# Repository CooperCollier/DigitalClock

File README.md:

# DigitalClock
A 12-hour digital clock made out of logic gates and flip-flops and implemented in Logisim.

This project incorporates the logisim 7-segment-display driver created here: https://github.com/marceloboeira/logisim-7-segment-display-driver.

How to open this project:

1: clone this repository with `git clone https://github.com/CooperCollier/DigitalClock --recursive`. The recursive tag is necessary to include the 7-segment-display driver.

2: Open the file clock.circ in logisim.

3: Under the 'simulate' tab, set 'tick frequency' to 2Hz.

4: Under the 'simulate' tab, set 'ticks enabled' to true.

How to use the clock:

Press the SET TIME button to make the clock enter or exit the SET TIME state. When the clock is in the SET TIME state, the SET TIME LED will be turned on. When the clock enters the SET TIME state, the time is immediately reset to 12:00 AM. 

Press the +MIN and +HOUR buttons to change the displayed time. These buttons are only active when the clock is in the SET TIME state.

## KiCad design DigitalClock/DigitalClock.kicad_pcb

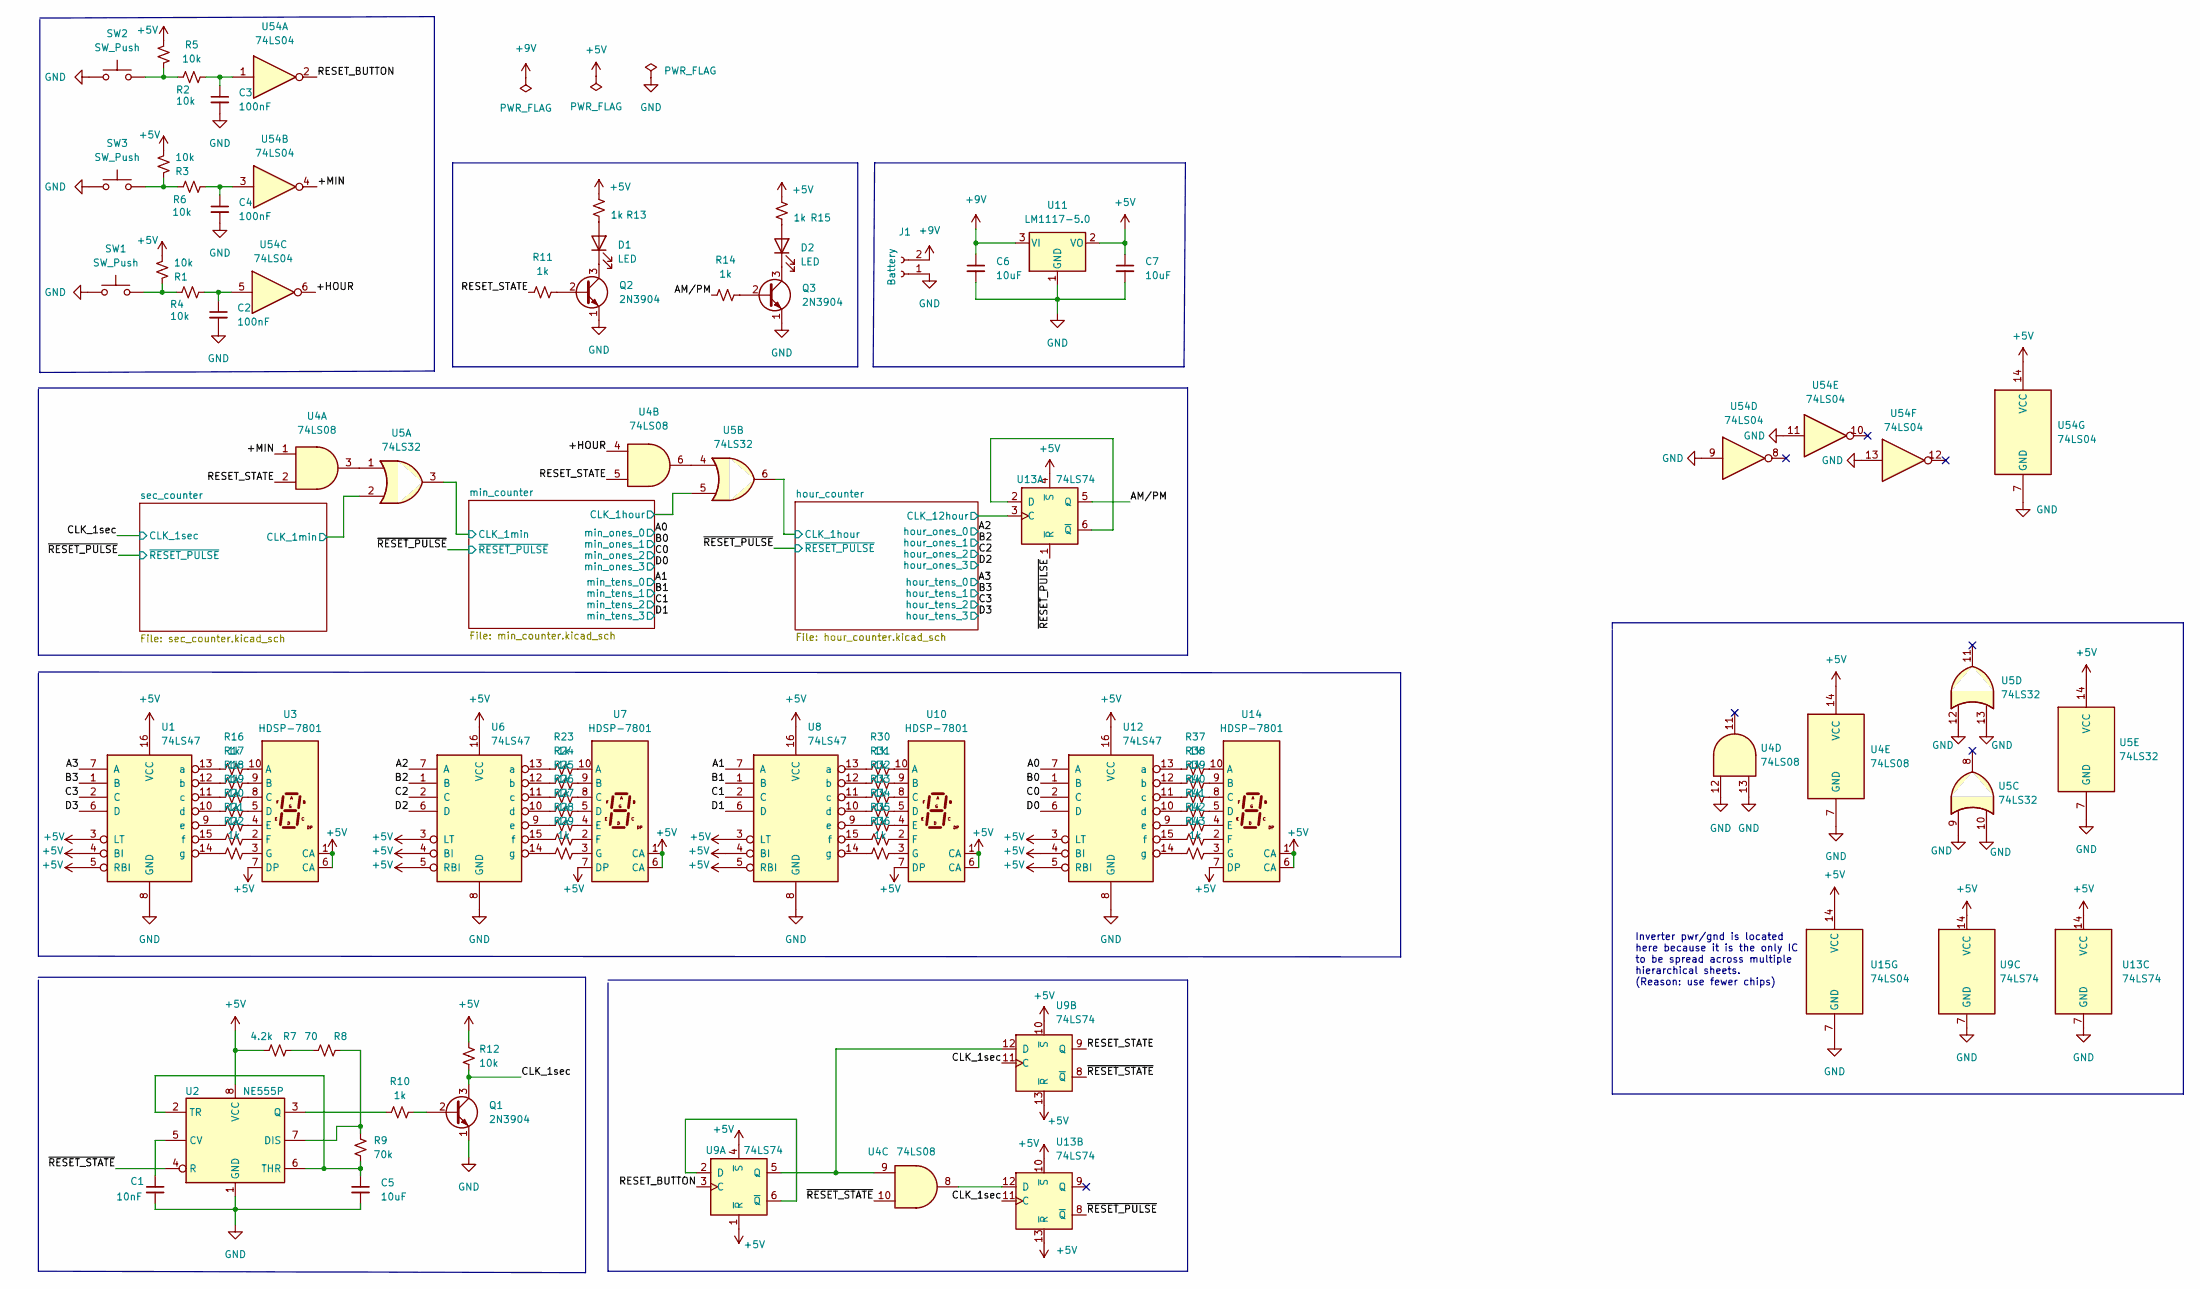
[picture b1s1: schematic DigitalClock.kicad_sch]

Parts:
C1: 10nF; C_Disc_D5.0mm_W2.5mm_P5.00mm
C2, C3, C4: 100nF; C_Disc_D5.0mm_W2.5mm_P5.00mm
C5, C6, C7: 10uF; CP_Radial_Tantal_D5.0mm_P5.00mm
D1, D2: LED; LED_D3.0mm
J1: Battery; TerminalBlock_Phoenix_MKDS-1,5-2_1x02_P5.00mm_Horizontal
Q1, Q2, Q3: 2N3904; TO-92_Inline
R1, R2, R3, R4, R5, R6, R12: 10k; R_Axial_DIN0207_L6.3mm_D2.5mm_P10.16mm_Horizontal
R7: 4.2k; R_Axial_DIN0207_L6.3mm_D2.5mm_P10.16mm_Horizontal
R8: 70; R_Axial_DIN0207_L6.3mm_D2.5mm_P10.16mm_Horizontal
R9: 70k; R_Axial_DIN0207_L6.3mm_D2.5mm_P10.16mm_Horizontal
R10, R11, R13, R14, R15, R16, R17, R18, R19, R20, R21, R22, R23, R24, R25, R26, R27, R28, R29, R30, R31, R32, R33, R34, R35, R36, R37, R38, R39, R40, R41, R42, R43: 1k; R_Axial_DIN0207_L6.3mm_D2.5mm_P10.16mm_Horizontal
SW1, SW2, SW3: SW_Push; SW_PUSH_6mm
U1, U6, U8, U12: 74LS47; DIP-16_W7.62mm
U2: NE555P; DIP-8_W7.62mm
U3, U7, U10, U14: HDSP-7801; 7SegmentLED_LTS6760_LTS6780
U4: 74LS08; DIP-14_W7.62mm
U5: 74LS32; DIP-14_W7.62mm
U9, U13: 74LS74; DIP-14_W7.62mm
U11: LM1117-5.0; TO-220-3_Vertical
U15, U54: 74LS04; DIP-14_W7.62mm

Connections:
+5V: C7.1, R1.2, R2.2, R3.2, R7.1, R12.2, R13.2, R15.2, U1.3 (LT), U1.4 (BI), U1.5 (RBI), U1.16 (VCC), U2.8 (VCC), U3.1 (CA), U3.6 (CA), U3.7 (DP), U4.14 (VCC), U5.14 (VCC), U6.3 (LT), U6.4 (BI), U6.5 (RBI), U6.16 (VCC), U7.1 (CA), U7.6 (CA), U7.7 (DP), U8.3 (LT), U8.4 (BI), U8.5 (RBI), U8.16 (VCC), U9.1 (~R), U9.4 (~S), U9.10 (~S), U9.13 (~R), U9.14 (VCC), U10.1 (CA), U10.6 (CA), U10.7 (DP), U11.2 (VO), U12.3 (LT), U12.4 (BI), U12.5 (RBI), U12.16 (VCC), U13.4 (~S), U13.10 (~S), U13.13 (~R), U13.14 (VCC), U14.1 (CA), U14.6 (CA), U14.7 (DP), U15.14 (VCC), U54.14 (VCC); also elsewhere on the board
+9V: C6.1, J1.2, U11.3 (VI)
/+HOUR: U4.4, U54.6
/+MIN: U4.1, U54.4
/A0: U12.7 (A); also elsewhere on the board
/A1: U8.7 (A); also elsewhere on the board
/A2: U6.7 (A); also elsewhere on the board
/A3: U1.7 (A); also elsewhere on the board
/AM/PM: R14.1, U13.5 (Q)
/B0: U12.1 (B); also elsewhere on the board
/B1: U8.1 (B); also elsewhere on the board
/B2: U6.1 (B); also elsewhere on the board
/B3: U1.1 (B); also elsewhere on the board
/C0: U12.2 (C); also elsewhere on the board
/C1: U8.2 (C); also elsewhere on the board
/C2: U6.2 (C); also elsewhere on the board
/C3: U1.2 (C); also elsewhere on the board
/CLK_1sec: Q1.3 (C), R12.1, U9.11 (C), U13.11 (C); also elsewhere on the board
/D0: U12.6 (D); also elsewhere on the board
/D1: U8.6 (D); also elsewhere on the board
/D2: U6.6 (D); also elsewhere on the board
/D3: U1.6 (D); also elsewhere on the board
/RESET_BUTTON: U9.3 (C), U54.2
/RESET_STATE: R11.1, U4.2, U4.5, U9.9 (Q)
/hour_counter/CLK_1hour: U5.6; also elsewhere on the board
/hour_counter/CLK_12hour: U13.3 (C); also elsewhere on the board
/min_counter/CLK_1hour: U5.5; also elsewhere on the board
/min_counter/CLK_1min: U5.3; also elsewhere on the board
/sec_counter/CLK_1min: U5.2; also elsewhere on the board
/~RESET_PULSE: U13.1 (~R), U13.8 (~Q); also elsewhere on the board
/~RESET_STATE: U2.4 (R), U4.10, U9.8 (~Q)
GND: C1.2, C2.2, C3.2, C4.2, C5.2, C6.2, C7.2, J1.1, Q1.1 (E), Q2.1 (E), Q3.1 (E), SW1.1, SW2.1, SW3.1, U1.8 (GND), U2.1 (GND), U4.7 (GND), U4.12, U4.13, U5.7 (GND), U5.9, U5.10, U5.12, U5.13, U6.8 (GND), U8.8 (GND), U9.7 (GND), U11.1 (GND), U12.8 (GND), U13.7 (GND), U15.7 (GND), U54.7 (GND), U54.9, U54.11, U54.13; also elsewhere on the board
unnamed: C1.1, U2.5 (CV)
unnamed: C2.1, R4.2, U54.5
unnamed: C3.1, R5.2, U54.1
unnamed: C4.1, R6.2, U54.3
unnamed: C5.1, R9.2, U2.2 (TR), U2.6 (THR)
unnamed: D1.1 (K), Q2.3 (C)
unnamed: D1.2 (A), R13.1
unnamed: D2.1 (K), Q3.3 (C)
unnamed: D2.2 (A), R15.1
unnamed: Q1.2 (B), R10.2
unnamed: Q2.2 (B), R11.2
unnamed: Q3.2 (B), R14.2
unnamed: R1.1, R4.1, SW1.2
unnamed: R2.1, R5.1, SW2.2
unnamed: R3.1, R6.1, SW3.2
unnamed: R7.2, R8.1
unnamed: R8.2, R9.1, U2.7 (DIS)
unnamed: R10.1, U2.3 (Q)
unnamed: R16.1, U1.13 (a)
unnamed: R16.2, U3.10 (A)
unnamed: R17.1, U1.12 (b)
unnamed: R17.2, U3.9 (B)
unnamed: R18.1, U1.11 (c)
unnamed: R18.2, U3.8 (C)
unnamed: R19.1, U1.10 (d)
unnamed: R19.2, U3.5 (D)
unnamed: R20.1, U1.9 (e)
unnamed: R20.2, U3.4 (E)
unnamed: R21.1, U1.15 (f)
unnamed: R21.2, U3.2 (F)
unnamed: R22.1, U1.14 (g)
unnamed: R22.2, U3.3 (G)
unnamed: R23.1, U6.13 (a)
unnamed: R23.2, U7.10 (A)
unnamed: R24.1, U6.12 (b)
unnamed: R24.2, U7.9 (B)
unnamed: R25.1, U6.11 (c)
unnamed: R25.2, U7.8 (C)
unnamed: R26.1, U6.10 (d)
unnamed: R26.2, U7.5 (D)
unnamed: R27.1, U6.9 (e)
unnamed: R27.2, U7.4 (E)
unnamed: R28.1, U6.15 (f)
unnamed: R28.2, U7.2 (F)
unnamed: R29.1, U6.14 (g)
unnamed: R29.2, U7.3 (G)
unnamed: R30.1, U8.13 (a)
unnamed: R30.2, U10.10 (A)
unnamed: R31.1, U8.12 (b)
unnamed: R31.2, U10.9 (B)
unnamed: R32.1, U8.11 (c)
unnamed: R32.2, U10.8 (C)
unnamed: R33.1, U8.10 (d)
unnamed: R33.2, U10.5 (D)
unnamed: R34.1, U8.9 (e)
unnamed: R34.2, U10.4 (E)
unnamed: R35.1, U8.15 (f)
unnamed: R35.2, U10.2 (F)
unnamed: R36.1, U8.14 (g)
unnamed: R36.2, U10.3 (G)
unnamed: R37.1, U12.13 (a)
unnamed: R37.2, U14.10 (A)
unnamed: R38.1, U12.12 (b)
unnamed: R38.2, U14.9 (B)
unnamed: R39.1, U12.11 (c)
unnamed: R39.2, U14.8 (C)
unnamed: R40.1, U12.10 (d)
unnamed: R40.2, U14.5 (D)
unnamed: R41.1, U12.9 (e)
unnamed: R41.2, U14.4 (E)
unnamed: R42.1, U12.15 (f)
unnamed: R42.2, U14.2 (F)
unnamed: R43.1, U12.14 (g)
unnamed: R43.2, U14.3 (G)
unnamed: U4.3, U5.1
unnamed: U4.6, U5.4
unnamed: U4.9, U9.5 (Q), U9.12 (D)
unnamed: U9.2 (D), U9.6 (~Q)
unnamed: U13.2 (D), U13.6 (~Q)
unnamed: U4.8, U13.12 (D)

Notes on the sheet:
Inverter pwr/gnd is located here because it is the only IC to be spread across multiple hierarchical sheets. (Reason: use fewer chips)

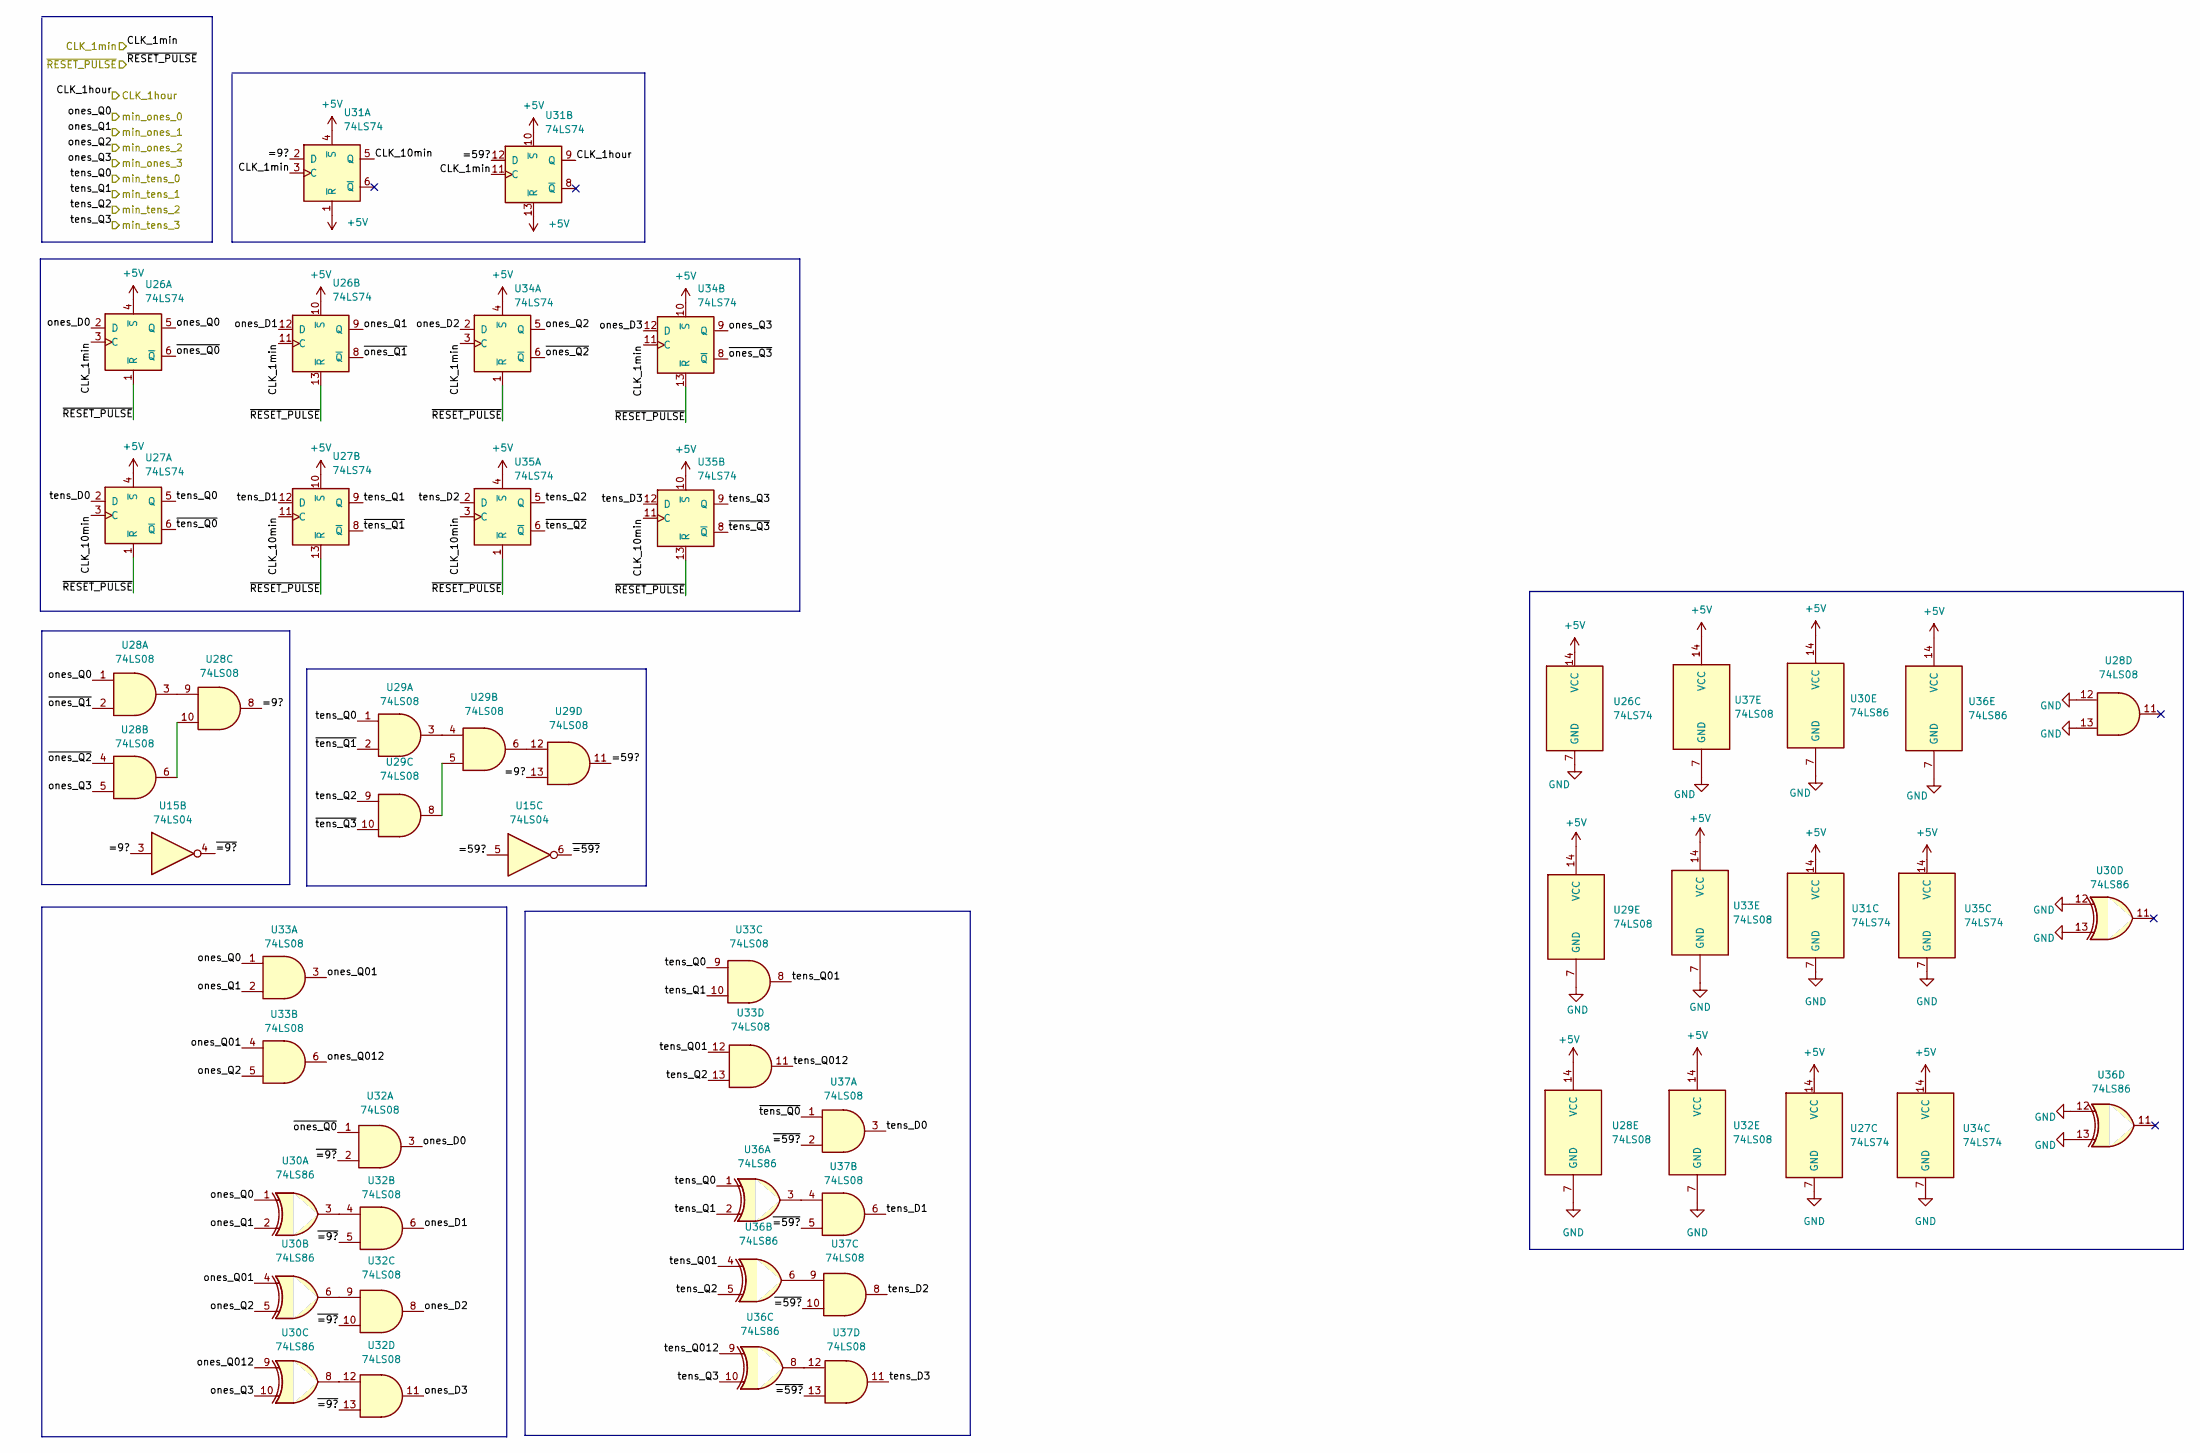
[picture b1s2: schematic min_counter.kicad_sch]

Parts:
U15: 74LS04; DIP-14_W7.62mm
U26, U27, U31, U34, U35: 74LS74; DIP-14_W7.62mm
U28, U29, U32, U33, U37: 74LS08; DIP-14_W7.62mm
U30, U36: 74LS86; DIP-14_W7.62mm

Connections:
+5V: U26.4 (~S), U26.10 (~S), U26.14 (VCC), U27.4 (~S), U27.10 (~S), U27.14 (VCC), U28.14 (VCC), U29.14 (VCC), U30.14 (VCC), U31.1 (~R), U31.4 (~S), U31.10 (~S), U31.13 (~R), U31.14 (VCC), U32.14 (VCC), U33.14 (VCC), U34.4 (~S), U34.10 (~S), U34.14 (VCC), U35.4 (~S), U35.10 (~S), U35.14 (VCC), U36.14 (VCC), U37.14 (VCC); also elsewhere on the board
/A0: U26.5 (Q), U28.1, U30.1, U33.1; also elsewhere on the board
/A1: U27.5 (Q), U29.1, U33.9, U36.1; also elsewhere on the board
/B0: U26.9 (Q), U30.2, U33.2; also elsewhere on the board
/B1: U27.9 (Q), U33.10, U36.2; also elsewhere on the board
/C0: U30.5, U33.5, U34.5 (Q); also elsewhere on the board
/C1: U29.9, U33.13, U35.5 (Q), U36.5; also elsewhere on the board
/D0: U28.5, U30.10, U34.9 (Q); also elsewhere on the board
/D1: U35.9 (Q), U36.10; also elsewhere on the board
/min_counter/=9?: U15.3, U28.8, U29.13, U31.2 (D)
/min_counter/=59?: U15.5, U29.11, U31.12 (D)
/min_counter/CLK_1hour: U31.9 (Q); also elsewhere on the board
/min_counter/CLK_1min: U26.3 (C), U26.11 (C), U31.3 (C), U31.11 (C), U34.3 (C), U34.11 (C); also elsewhere on the board
/min_counter/CLK_10min: U27.3 (C), U27.11 (C), U31.5 (Q), U35.3 (C), U35.11 (C)
/min_counter/ones_D0: U26.2 (D), U32.3
/min_counter/ones_D1: U26.12 (D), U32.6
/min_counter/ones_D2: U32.8, U34.2 (D)
/min_counter/ones_D3: U32.11, U34.12 (D)
/min_counter/ones_Q01: U30.4, U33.3, U33.4
/min_counter/ones_Q012: U30.9, U33.6
/min_counter/tens_D0: U27.2 (D), U37.3
/min_counter/tens_D1: U27.12 (D), U37.6
/min_counter/tens_D2: U35.2 (D), U37.8
/min_counter/tens_D3: U35.12 (D), U37.11
/min_counter/tens_Q01: U33.8, U33.12, U36.4
/min_counter/tens_Q012: U33.11, U36.9
/min_counter/~=9?: U15.4, U32.2, U32.5, U32.10, U32.13
/min_counter/~=59?: U15.6, U37.2, U37.5, U37.10, U37.13
/min_counter/~ones_Q0: U26.6 (~Q), U32.1
/min_counter/~ones_Q1: U26.8 (~Q), U28.2
/min_counter/~ones_Q2: U28.4, U34.6 (~Q)
/min_counter/~ones_Q3: U34.8 (~Q)
/min_counter/~tens_Q0: U27.6 (~Q), U37.1
/min_counter/~tens_Q1: U27.8 (~Q), U29.2
/min_counter/~tens_Q2: U35.6 (~Q)
/min_counter/~tens_Q3: U29.10, U35.8 (~Q)
/~RESET_PULSE: U26.1 (~R), U26.13 (~R), U27.1 (~R), U27.13 (~R), U34.1 (~R), U34.13 (~R), U35.1 (~R), U35.13 (~R); also elsewhere on the board
GND: U26.7 (GND), U27.7 (GND), U28.7 (GND), U28.12, U28.13, U29.7 (GND), U30.7 (GND), U30.12, U30.13, U31.7 (GND), U32.7 (GND), U33.7 (GND), U34.7 (GND), U35.7 (GND), U36.7 (GND), U36.12, U36.13, U37.7 (GND); also elsewhere on the board
unnamed: U28.3, U28.9
unnamed: U28.6, U28.10
unnamed: U29.3, U29.4
unnamed: U29.5, U29.8
unnamed: U29.6, U29.12
unnamed: U30.3, U32.4
unnamed: U30.6, U32.9
unnamed: U30.8, U32.12
unnamed: U36.3, U37.4
unnamed: U36.6, U37.9
unnamed: U36.8, U37.12

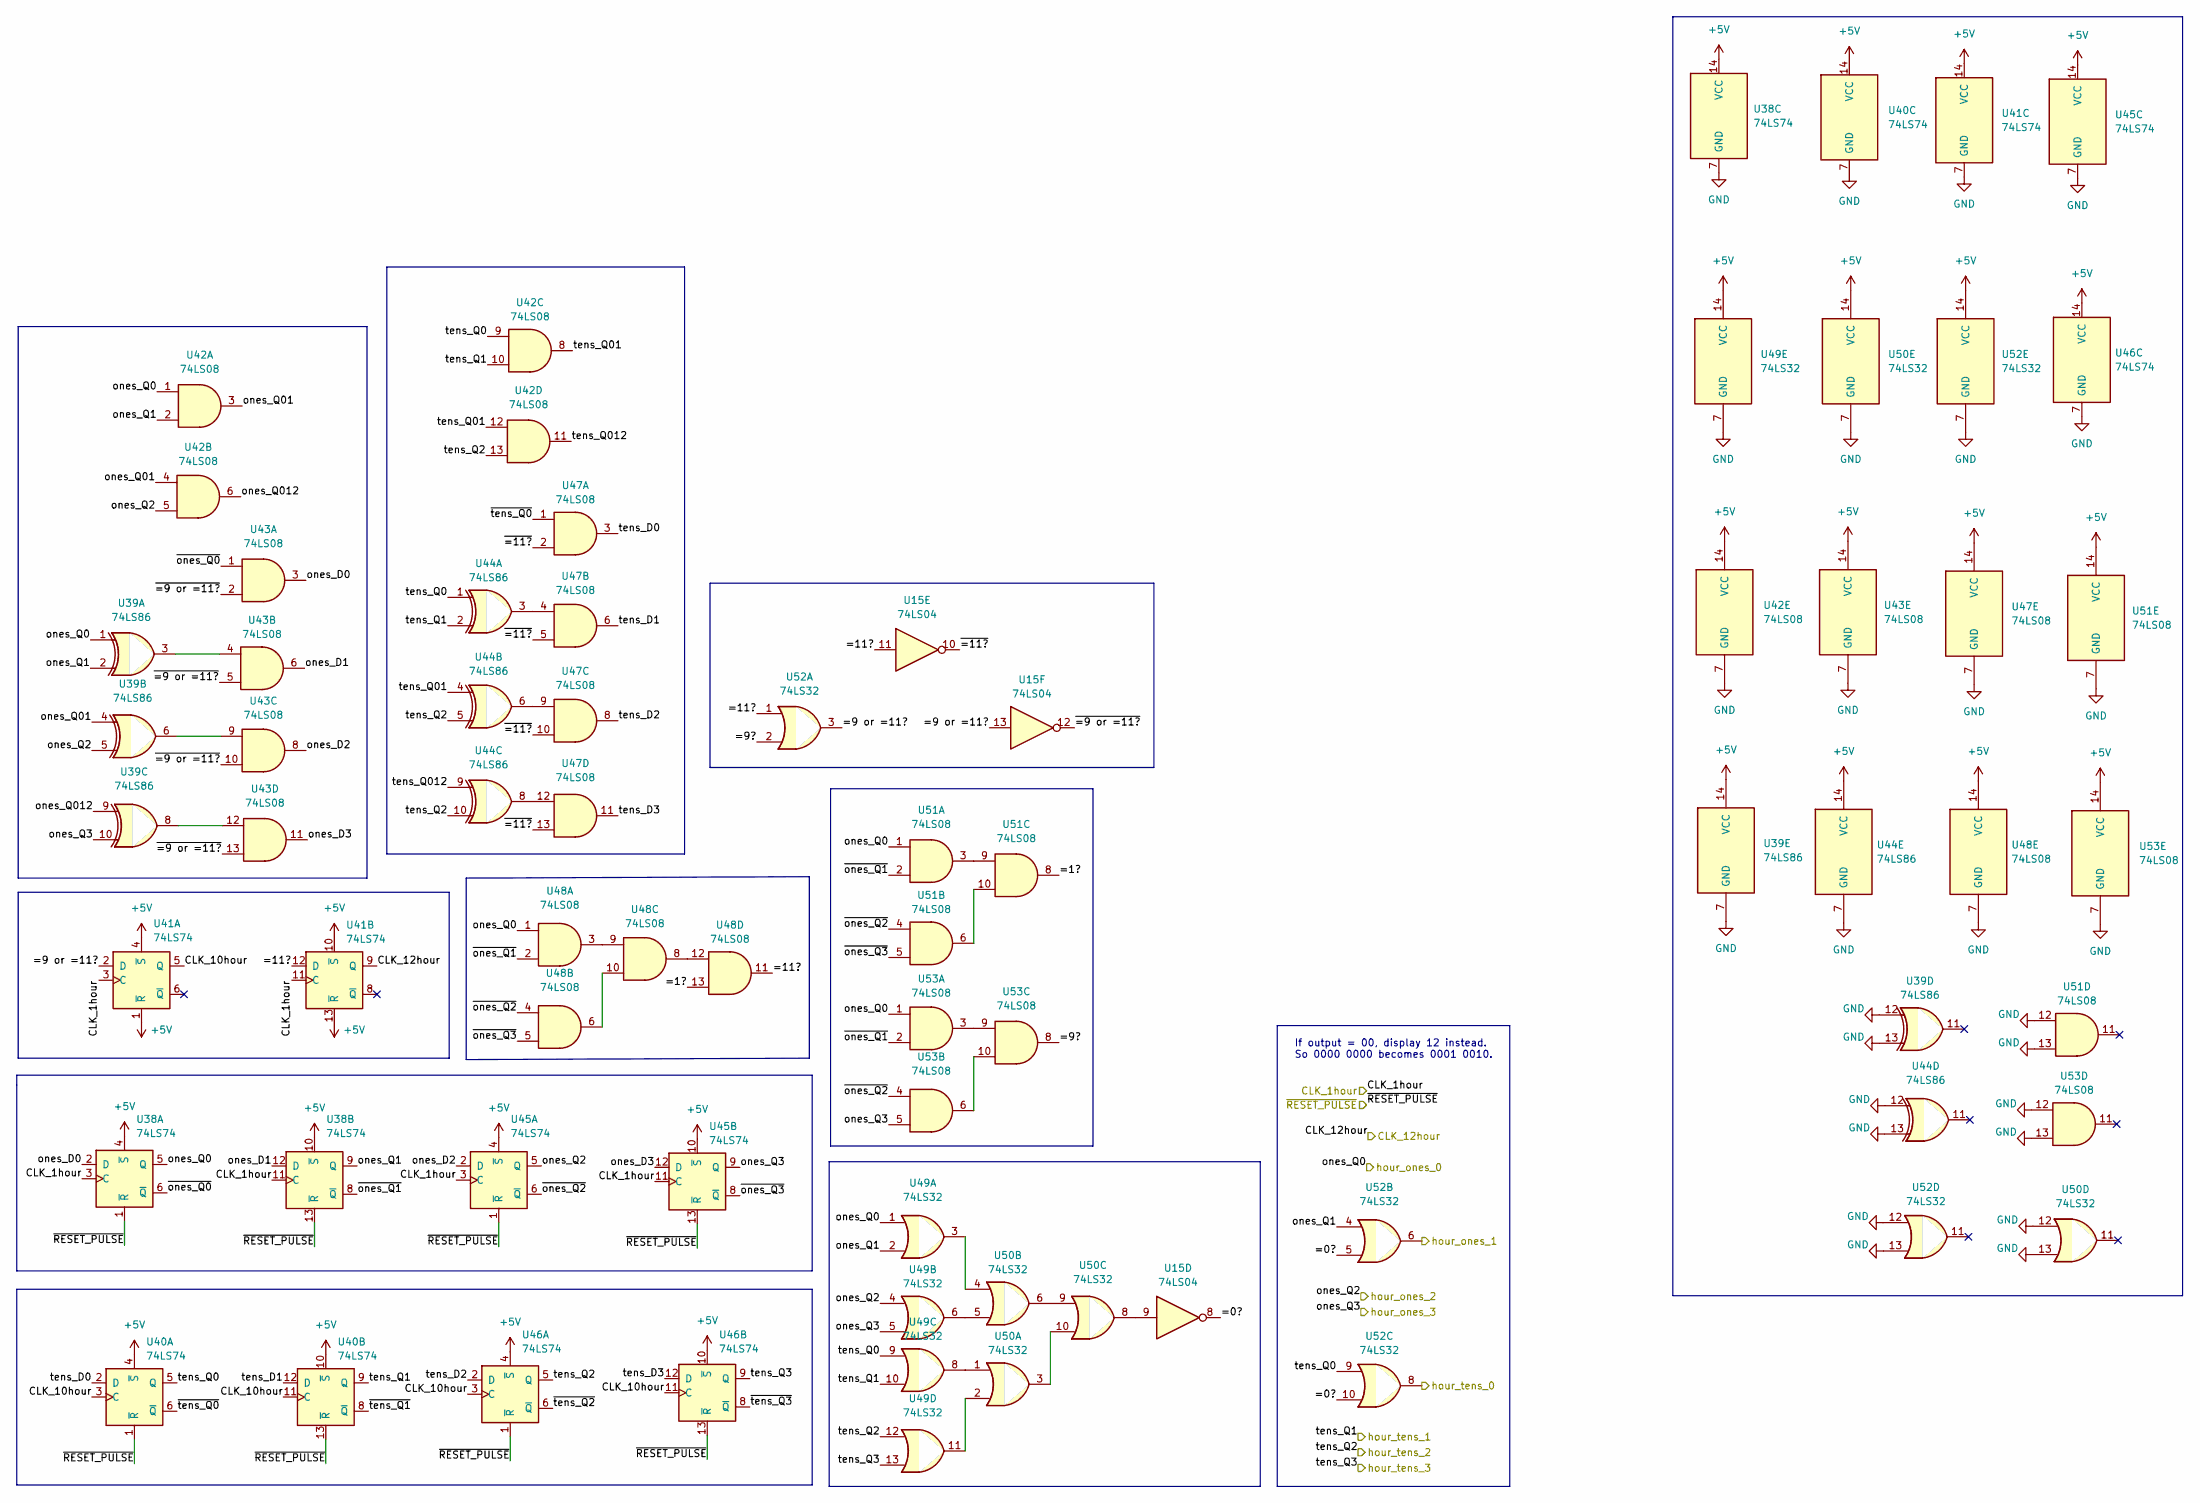
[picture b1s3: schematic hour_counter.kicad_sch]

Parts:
U15: 74LS04; DIP-14_W7.62mm
U38, U40, U41, U45, U46: 74LS74; DIP-14_W7.62mm
U39, U44: 74LS86; DIP-14_W7.62mm
U42, U43, U47, U48, U51, U53: 74LS08; DIP-14_W7.62mm
U49, U50, U52: 74LS32; DIP-14_W7.62mm

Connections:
+5V: U38.4 (~S), U38.10 (~S), U38.14 (VCC), U39.14 (VCC), U40.4 (~S), U40.10 (~S), U40.14 (VCC), U41.1 (~R), U41.4 (~S), U41.10 (~S), U41.13 (~R), U41.14 (VCC), U42.14 (VCC), U43.14 (VCC), U44.14 (VCC), U45.4 (~S), U45.10 (~S), U45.14 (VCC), U46.4 (~S), U46.10 (~S), U46.14 (VCC), U47.14 (VCC), U48.14 (VCC), U49.14 (VCC), U50.14 (VCC), U51.14 (VCC), U52.14 (VCC), U53.14 (VCC); also elsewhere on the board
/A2: U38.5 (Q), U39.1, U42.1, U48.1, U49.1, U51.1, U53.1; also elsewhere on the board
/A3: U52.8; also elsewhere on the board
/B2: U52.6; also elsewhere on the board
/B3: U40.9 (Q), U42.10, U44.2, U49.10; also elsewhere on the board
/C2: U39.5, U42.5, U45.5 (Q), U49.4; also elsewhere on the board
/C3: U42.13, U44.5, U44.10, U46.5 (Q), U49.12; also elsewhere on the board
/D2: U39.10, U45.9 (Q), U49.5, U53.5; also elsewhere on the board
/D3: U46.9 (Q), U49.13; also elsewhere on the board
/hour_counter/=0?: U15.8, U52.5, U52.10
/hour_counter/=1?: U48.13, U51.8
/hour_counter/=9 or =11?: U15.13, U41.2 (D), U52.3
/hour_counter/=9?: U52.2, U53.8
/hour_counter/=11?: U15.11, U41.12 (D), U48.11, U52.1
/hour_counter/CLK_1hour: U38.3 (C), U38.11 (C), U41.3 (C), U41.11 (C), U45.3 (C), U45.11 (C); also elsewhere on the board
/hour_counter/CLK_10hour: U40.3 (C), U40.11 (C), U41.5 (Q), U46.3 (C), U46.11 (C)
/hour_counter/CLK_12hour: U41.9 (Q); also elsewhere on the board
/hour_counter/ones_D0: U38.2 (D), U43.3
/hour_counter/ones_D1: U38.12 (D), U43.6
/hour_counter/ones_D2: U43.8, U45.2 (D)
/hour_counter/ones_D3: U43.11, U45.12 (D)
/hour_counter/ones_Q1: U38.9 (Q), U39.2, U42.2, U49.2, U52.4
/hour_counter/ones_Q01: U39.4, U42.3, U42.4
/hour_counter/ones_Q012: U39.9, U42.6
/hour_counter/tens_D0: U40.2 (D), U47.3
/hour_counter/tens_D1: U40.12 (D), U47.6
/hour_counter/tens_D2: U46.2 (D), U47.8
/hour_counter/tens_D3: U46.12 (D), U47.11
/hour_counter/tens_Q0: U40.5 (Q), U42.9, U44.1, U49.9, U52.9
/hour_counter/tens_Q01: U42.8, U42.12, U44.4
/hour_counter/tens_Q012: U42.11, U44.9
/hour_counter/~=9 or =11?: U15.12, U43.2, U43.5, U43.10, U43.13
/hour_counter/~=11?: U15.10, U47.2, U47.5, U47.10, U47.13
/hour_counter/~ones_Q0: U38.6 (~Q), U43.1
/hour_counter/~ones_Q1: U38.8 (~Q), U48.2, U51.2, U53.2
/hour_counter/~ones_Q2: U45.6 (~Q), U48.4, U51.4, U53.4
/hour_counter/~ones_Q3: U45.8 (~Q), U48.5, U51.5
/hour_counter/~tens_Q0: U40.6 (~Q), U47.1
/hour_counter/~tens_Q1: U40.8 (~Q)
/hour_counter/~tens_Q2: U46.6 (~Q)
/hour_counter/~tens_Q3: U46.8 (~Q)
/~RESET_PULSE: U38.1 (~R), U38.13 (~R), U40.1 (~R), U40.13 (~R), U45.1 (~R), U45.13 (~R), U46.1 (~R), U46.13 (~R); also elsewhere on the board
GND: U38.7 (GND), U39.7 (GND), U39.12, U39.13, U40.7 (GND), U41.7 (GND), U42.7 (GND), U43.7 (GND), U44.7 (GND), U44.12, U44.13, U45.7 (GND), U46.7 (GND), U47.7 (GND), U48.7 (GND), U49.7 (GND), U50.7 (GND), U50.12, U50.13, U51.7 (GND), U51.12, U51.13, U52.7 (GND), U52.12, U52.13, U53.7 (GND), U53.12, U53.13; also elsewhere on the board
unnamed: U15.9, U50.8
unnamed: U39.3, U43.4
unnamed: U39.6, U43.9
unnamed: U39.8, U43.12
unnamed: U44.3, U47.4
unnamed: U44.6, U47.9
unnamed: U44.8, U47.12
unnamed: U48.3, U48.9
unnamed: U48.6, U48.10
unnamed: U48.8, U48.12
unnamed: U49.3, U50.4
unnamed: U49.6, U50.5
unnamed: U49.8, U50.1
unnamed: U49.11, U50.2
unnamed: U50.6, U50.9
unnamed: U50.3, U50.10
unnamed: U51.3, U51.9
unnamed: U51.6, U51.10
unnamed: U53.3, U53.9
unnamed: U53.6, U53.10

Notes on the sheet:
If output = 00, display 12 instead. So 0000 0000 becomes 0001 0010.

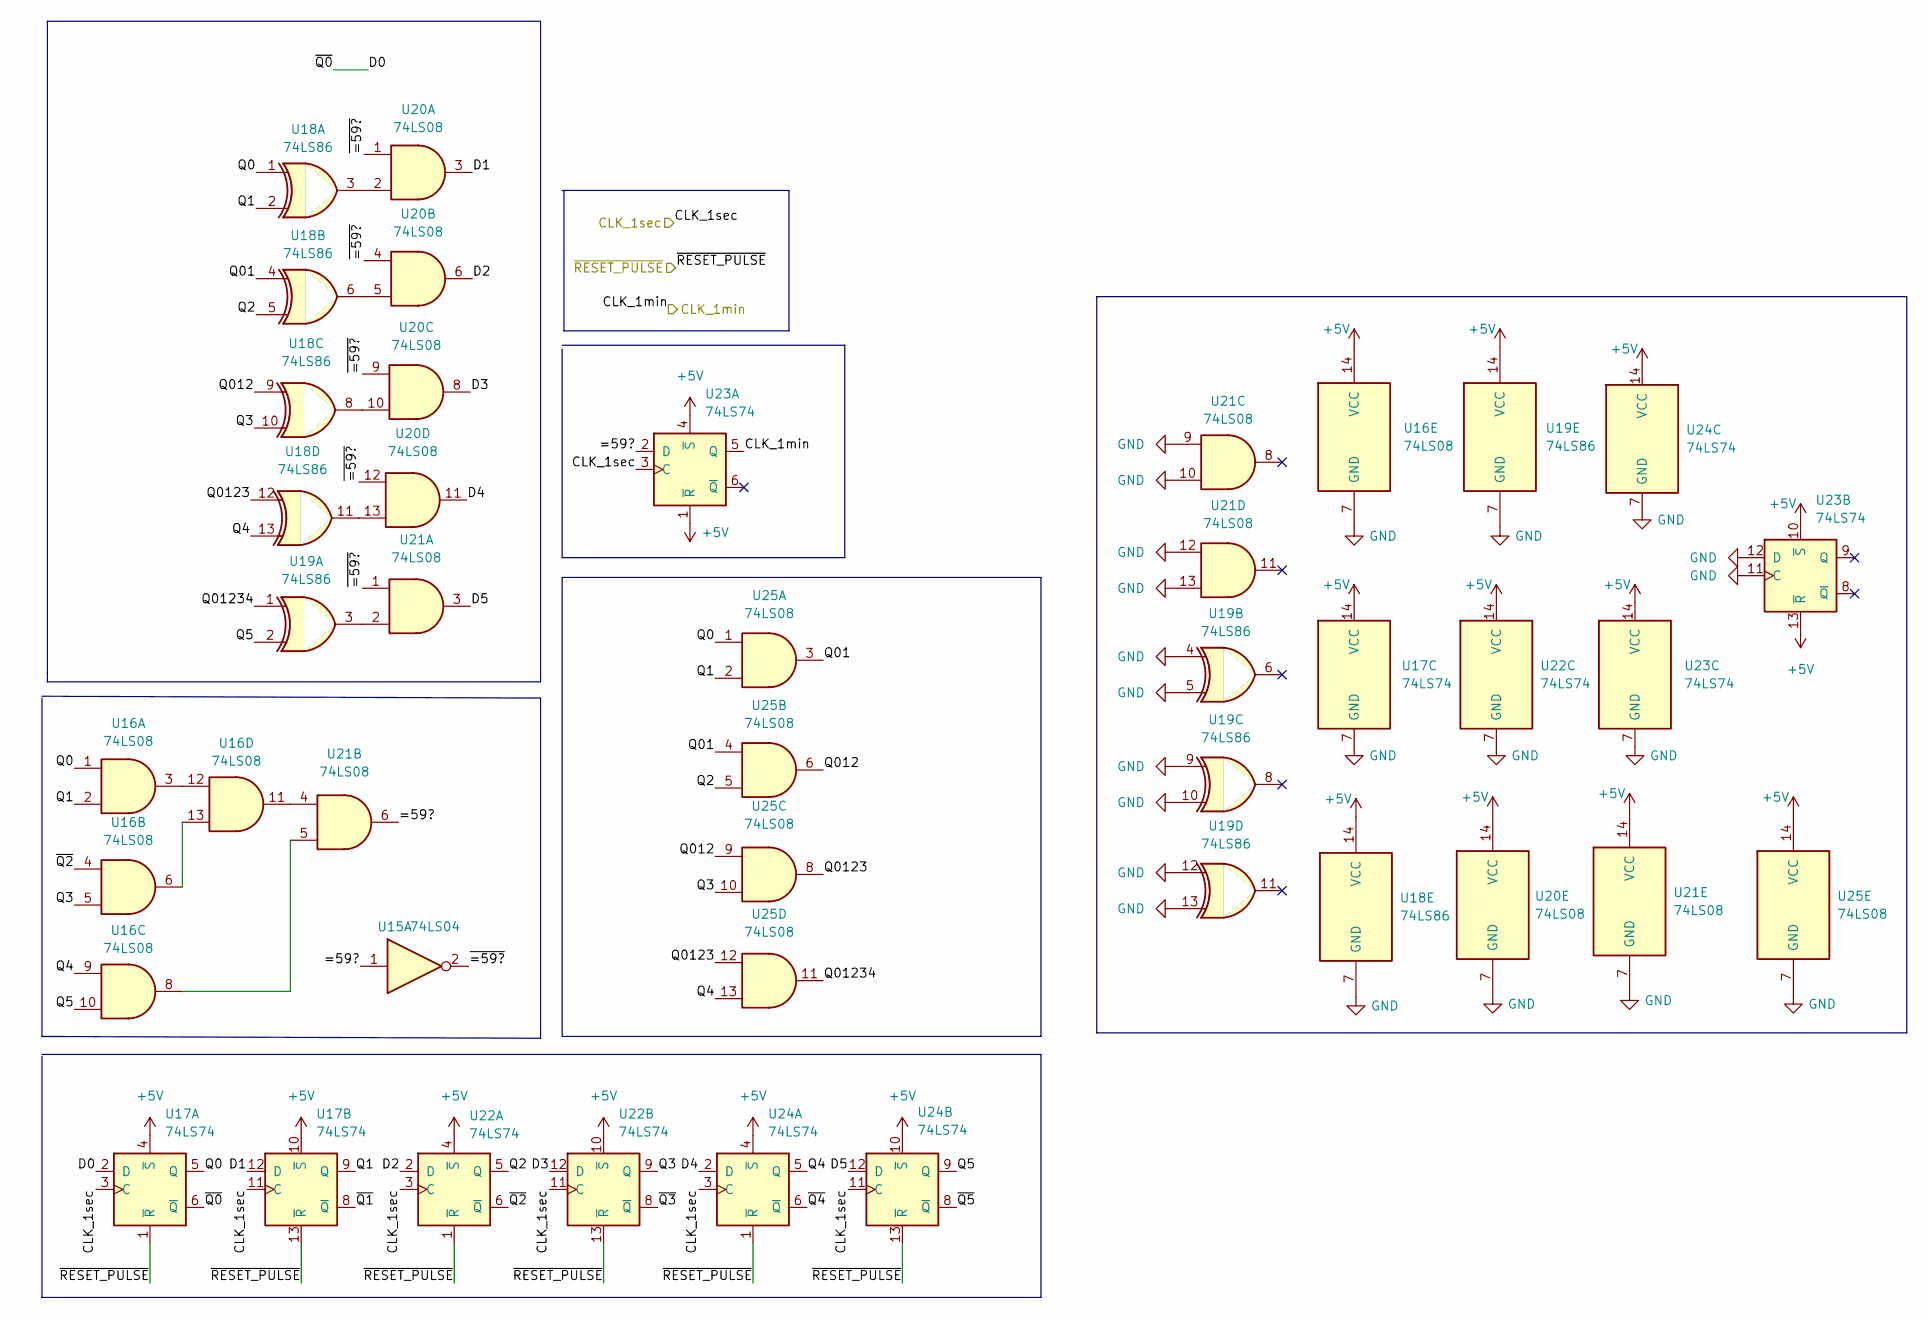
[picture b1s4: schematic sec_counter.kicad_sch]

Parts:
U15: 74LS04; DIP-14_W7.62mm
U16, U20, U21, U25: 74LS08; DIP-14_W7.62mm
U17, U22, U23, U24: 74LS74; DIP-14_W7.62mm
U18, U19: 74LS86; DIP-14_W7.62mm

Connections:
+5V: U16.14 (VCC), U17.4 (~S), U17.10 (~S), U17.14 (VCC), U18.14 (VCC), U19.14 (VCC), U20.14 (VCC), U21.14 (VCC), U22.4 (~S), U22.10 (~S), U22.14 (VCC), U23.1 (~R), U23.4 (~S), U23.10 (~S), U23.13 (~R), U23.14 (VCC), U24.4 (~S), U24.10 (~S), U24.14 (VCC), U25.14 (VCC); also elsewhere on the board
/CLK_1sec: U17.3 (C), U17.11 (C), U22.3 (C), U22.11 (C), U23.3 (C), U24.3 (C), U24.11 (C); also elsewhere on the board
/sec_counter/=59?: U15.1, U21.6, U23.2 (D)
/sec_counter/CLK_1min: U23.5 (Q); also elsewhere on the board
/sec_counter/D0: U17.2 (D), U17.6 (~Q)
/sec_counter/D1: U17.12 (D), U20.3
/sec_counter/D2: U20.6, U22.2 (D)
/sec_counter/D3: U20.8, U22.12 (D)
/sec_counter/D4: U20.11, U24.2 (D)
/sec_counter/D5: U21.3, U24.12 (D)
/sec_counter/Q0: U16.1, U17.5 (Q), U18.1, U25.1
/sec_counter/Q1: U16.2, U17.9 (Q), U18.2, U25.2
/sec_counter/Q01: U18.4, U25.3, U25.4
/sec_counter/Q2: U18.5, U22.5 (Q), U25.5
/sec_counter/Q3: U16.5, U18.10, U22.9 (Q), U25.10
/sec_counter/Q4: U16.9, U18.13, U24.5 (Q), U25.13
/sec_counter/Q5: U16.10, U19.2, U24.9 (Q)
/sec_counter/Q012: U18.9, U25.6, U25.9
/sec_counter/Q0123: U18.12, U25.8, U25.12
/sec_counter/Q01234: U19.1, U25.11
/sec_counter/~=59?: U15.2, U20.1, U20.4, U20.9, U20.12, U21.1
/sec_counter/~Q1: U17.8 (~Q)
/sec_counter/~Q2: U16.4, U22.6 (~Q)
/sec_counter/~Q3: U22.8 (~Q)
/sec_counter/~Q4: U24.6 (~Q)
/sec_counter/~Q5: U24.8 (~Q)
/~RESET_PULSE: U17.1 (~R), U17.13 (~R), U22.1 (~R), U22.13 (~R), U24.1 (~R), U24.13 (~R); also elsewhere on the board
GND: U16.7 (GND), U17.7 (GND), U18.7 (GND), U19.4, U19.5, U19.7 (GND), U19.9, U19.10, U19.12, U19.13, U20.7 (GND), U21.7 (GND), U21.9, U21.10, U21.12, U21.13, U22.7 (GND), U23.7 (GND), U23.11 (C), U23.12 (D), U24.7 (GND), U25.7 (GND); also elsewhere on the board
unnamed: U16.8, U21.5
unnamed: U16.11, U21.4
unnamed: U16.3, U16.12
unnamed: U16.6, U16.13
unnamed: U18.3, U20.2
unnamed: U18.6, U20.5
unnamed: U18.8, U20.10
unnamed: U18.11, U20.13
unnamed: U19.3, U21.2

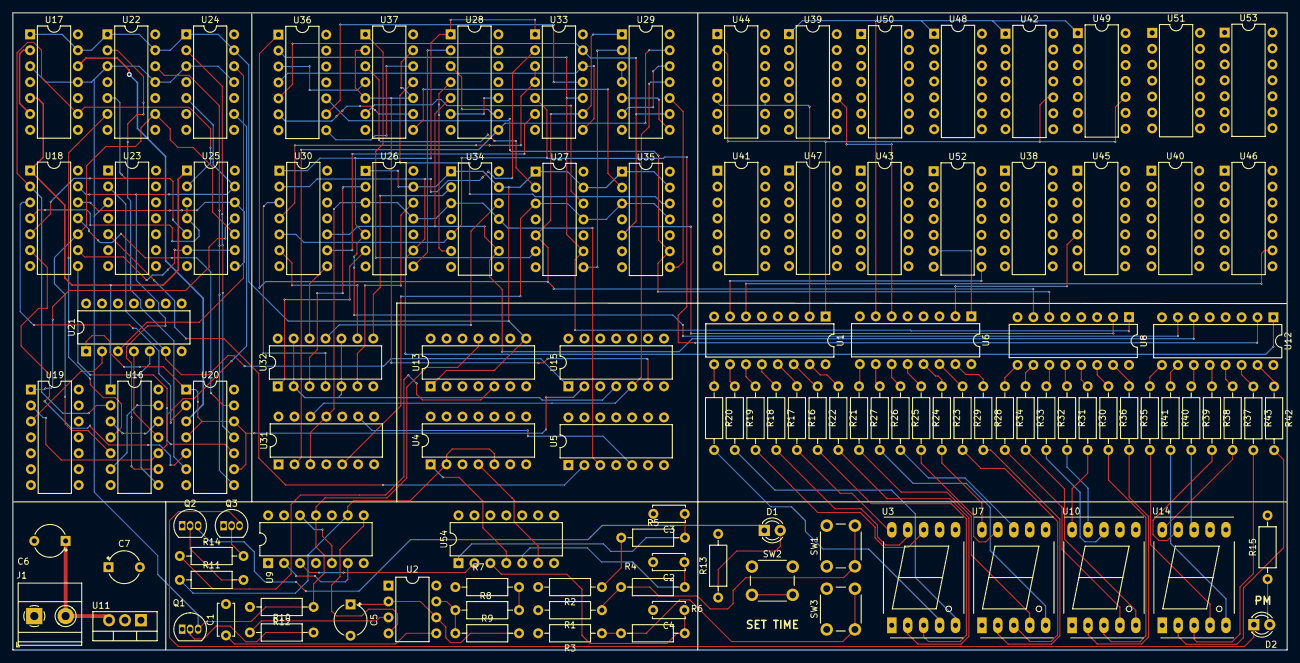
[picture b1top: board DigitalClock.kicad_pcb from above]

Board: 2 copper layers, 203.2 x 101.6 mm, 113 parts (0 on the bottom side), 221 nets.

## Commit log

2022-12-28 removed mux
2022-12-28 added transistors
2023-01-02 added kicad files
2023-01-02 added minute counter schematic"
2023-01-03 finished kicad schematic
2023-01-03 about to begin layout
2023-01-03 more routing
2023-01-05 more layout
2023-01-05 started routing
2023-01-05 finished pcb
2023-01-05 created bom and gerbers
2023-01-05 small updates to board
